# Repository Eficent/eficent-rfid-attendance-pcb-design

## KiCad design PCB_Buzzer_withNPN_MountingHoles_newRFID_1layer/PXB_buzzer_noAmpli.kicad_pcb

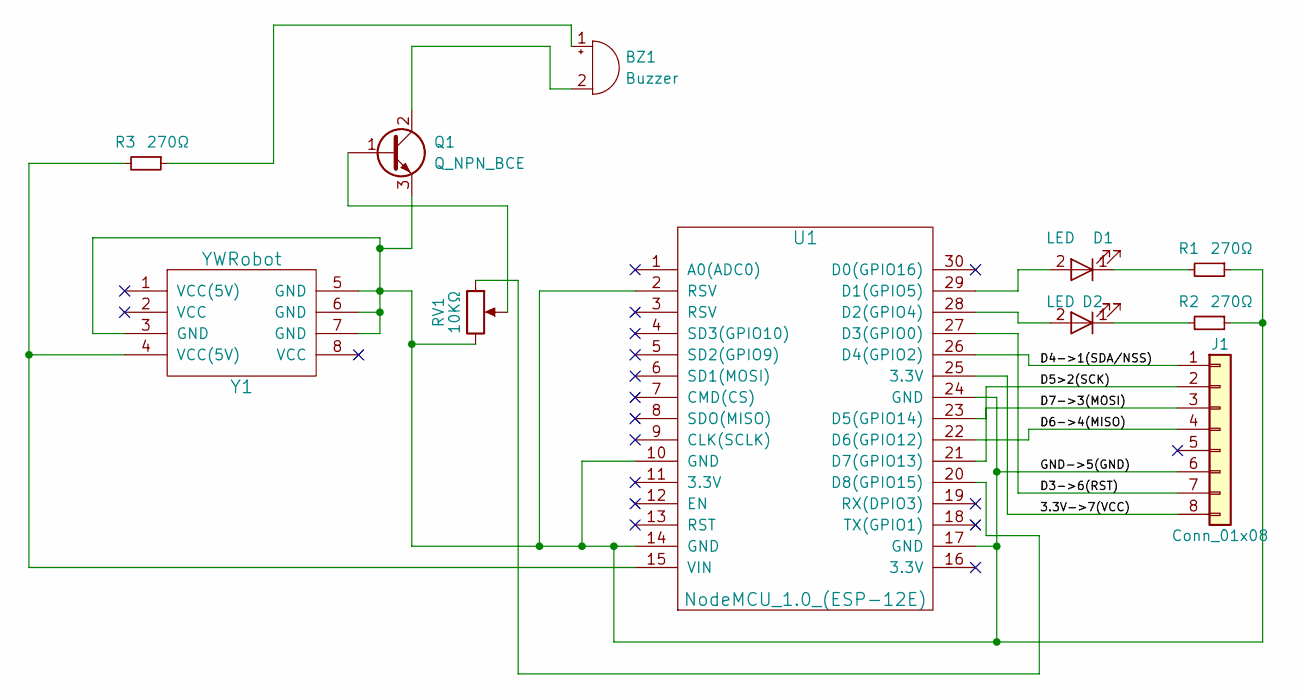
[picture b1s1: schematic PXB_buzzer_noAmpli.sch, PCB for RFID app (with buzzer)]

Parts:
BZ1: Buzzer; BUZZER_22mm
D1, D2: LED; LED_D5.0mm
J1: Conn_01x08; Pin_Header_Straight_1x08_Pitch2.54mm
Q1: Q_NPN_BCE; TO-92_Inline_Narrow_Oval_EBC
R1, R2, R3: 270Ω; R_Axial_DIN0207_L6.3mm_D2.5mm_P10.16mm_Horizontal
RV1: 10KΩ; Potentiometer_Trimmer_Piher_PT-10v10_Horizontal_Px10.0mm_Py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
U1: NodeMCU_1.0_(ESP-12E); NodeMCU1.0(12-E)
Y1: YWRobot; YWRobot2

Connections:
/3.3V->7(VCC): J1.8, U1.25 (3.3V)
/D3->6(RST): J1.7, U1.27 (D3(GPIO0))
/D4->1(SDA/NSS): J1.1, U1.26 (D4(GPIO2))
/D5>2(SCK): J1.2, U1.23 (D5(GPIO14))
/D6->4(MISO): J1.4, U1.22 (D6(GPIO12))
/D7->3(MOSI): J1.3, U1.21 (D7(GPIO13))
/GND->5(GND): J1.6, Q1.3 (E), R1.1, R2.1, RV1.3, U1.2 (RSV), U1.10 (GND), U1.14 (GND), U1.17 (GND), U1.24 (GND), Y1.3 (GND), Y1.5 (GND), Y1.6 (GND), Y1.7 (GND)
unnamed: BZ1.1 (-), R3.1
unnamed: BZ1.2 (+), Q1.2 (C)
unnamed: D1.1 (K), R1.2
unnamed: D1.2 (A), U1.29 (D1(GPIO5))
unnamed: D2.1 (K), R2.2
unnamed: D2.2 (A), U1.28 (D2(GPIO4))
unnamed: Q1.1 (B), RV1.2
unnamed: R3.2, U1.15 (VIN), Y1.4 (VCC(5V))
unnamed: RV1.1, U1.20 (D8(GPIO15))

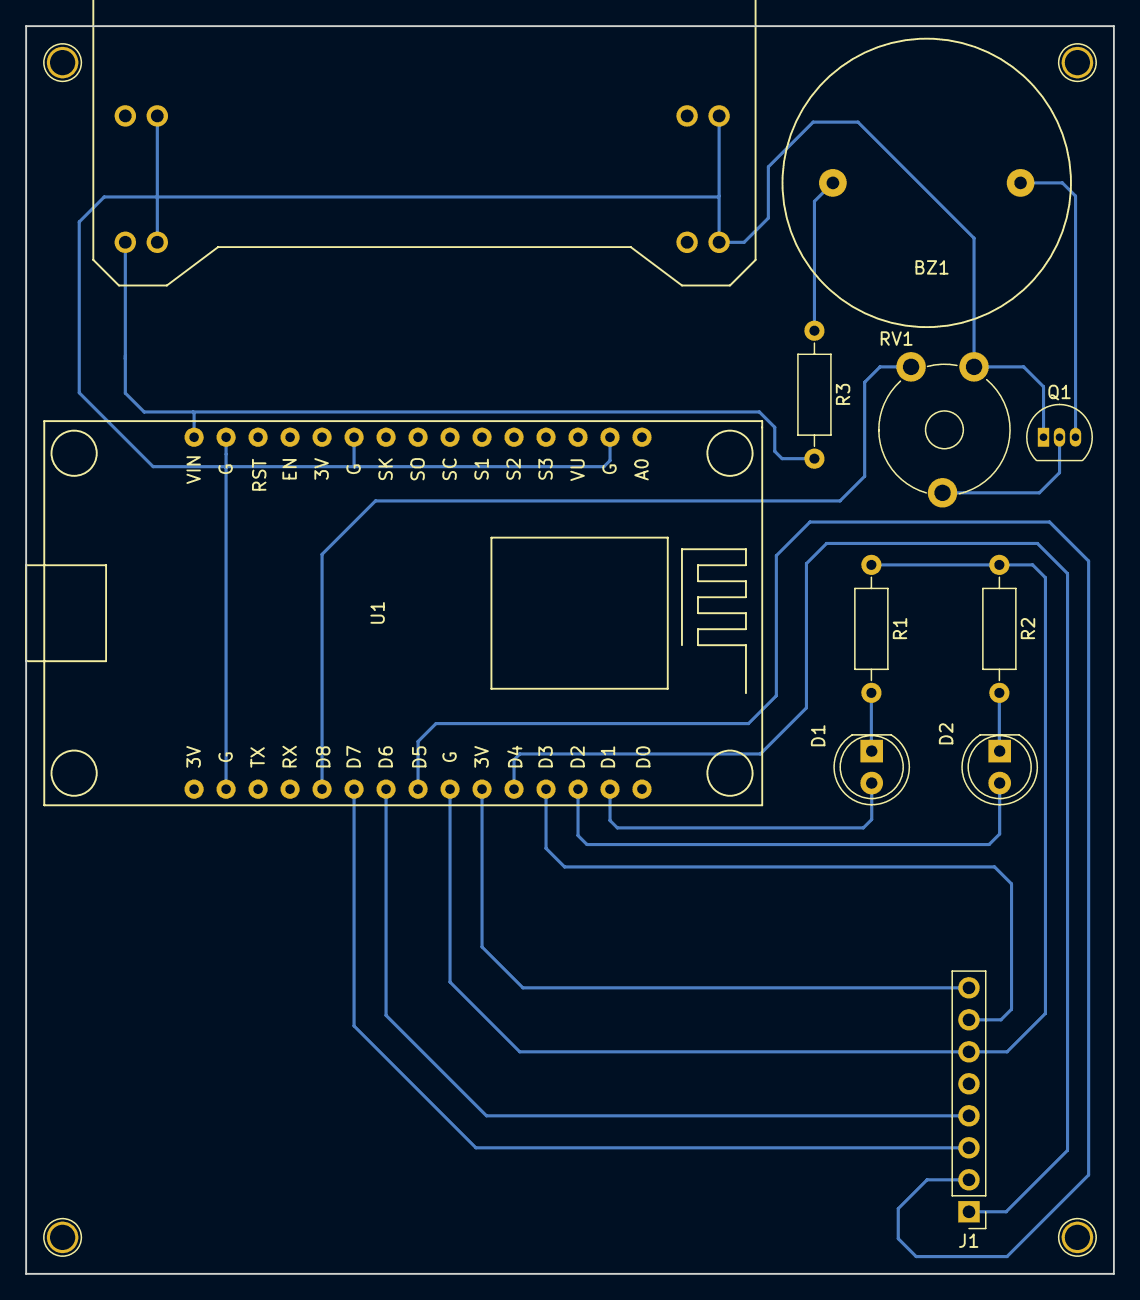
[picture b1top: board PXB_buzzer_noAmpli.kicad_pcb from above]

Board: 2 copper layers, 86.4 x 99.1 mm, 11 parts (0 on the bottom side), 16 nets.

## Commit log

2018-04-09 Final PCB Design
2018-06-07 ywrobot moved
